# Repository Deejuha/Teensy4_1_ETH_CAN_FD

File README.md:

Teensy 4.1 shield with Ethernet, CAN FD and 2x CAN.

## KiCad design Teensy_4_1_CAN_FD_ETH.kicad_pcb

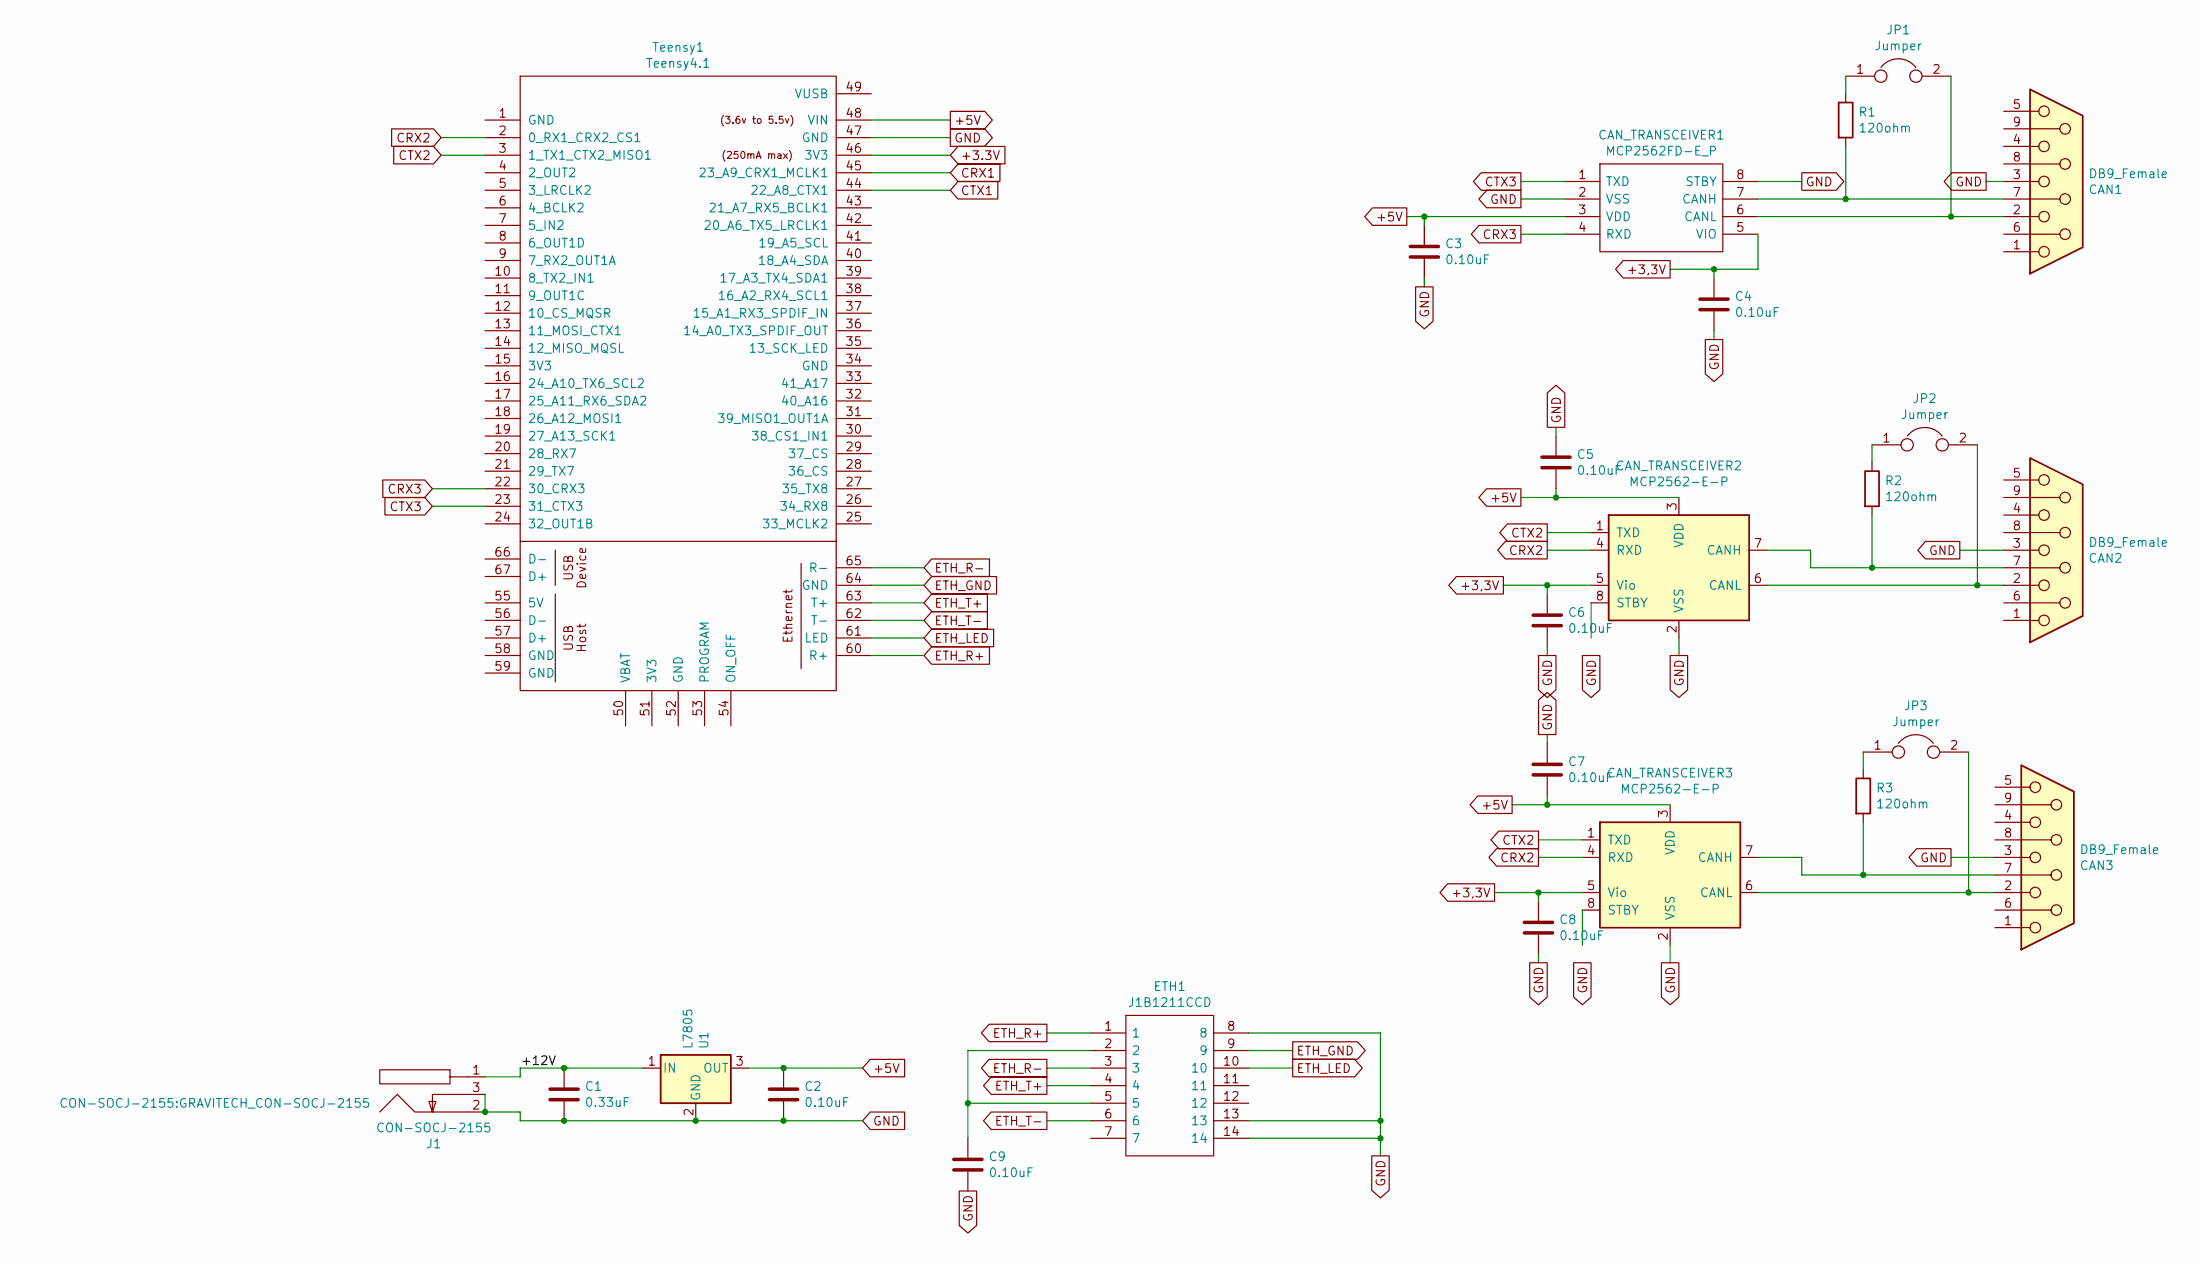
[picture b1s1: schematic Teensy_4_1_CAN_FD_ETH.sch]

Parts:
C1: 0.33uF; C_0603_1608Metric
C2, C3, C4, C5, C6, C7, C8, C9: 0.10uF; C_0603_1608Metric
CAN1, CAN2, CAN3: DB9_Female; DSUB-9_Female_Vertical_P2.77x2.84mm
CAN_TRANSCEIVER1: MCP2562FD-E_P; DIP787W46P254L927H533Q8; Mouser Part Number 579-MCP2562FD-E/P
CAN_TRANSCEIVER2, CAN_TRANSCEIVER3: MCP2562-E-P; DIP-8_W7.62mm
ETH1: J1B1211CCD; Mouser Part Number 950-J1B1211CCD
J1: CON-SOCJ-2155; GRAVITECH_CON-SOCJ-2155; Mouser Part Number 992-CON-SOCJ-2155
JP1, JP2, JP3: Jumper; PinSocket_1x02_P2.54mm_Vertical
R1, R2, R3: 120ohm; R_0603_1608Metric
Teensy1: Teensy4.1; Teensy41
U1: L7805; TO-220-3_Vertical

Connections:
+3,3V: C4.1, C6.1, C8.1, CAN_TRANSCEIVER1.5 (VIO), CAN_TRANSCEIVER2.5 (Vio), CAN_TRANSCEIVER3.5 (Vio)
+3.3V: Teensy1.46 (3V3)
+5V: C2.1, C3.1, C5.2, C7.2, CAN_TRANSCEIVER1.3 (VDD), CAN_TRANSCEIVER2.3 (VDD), CAN_TRANSCEIVER3.3 (VDD), Teensy1.48 (VIN), U1.3 (OUT)
/+12V: C1.1, J1.1, U1.1 (IN)
CRX1: Teensy1.45 (23_A9_CRX1_MCLK1)
CRX2: CAN_TRANSCEIVER2.4 (RXD), CAN_TRANSCEIVER3.4 (RXD), Teensy1.2 (0_RX1_CRX2_CS1)
CRX3: CAN_TRANSCEIVER1.4 (RXD), Teensy1.22 (30_CRX3)
CTX1: Teensy1.44 (22_A8_CTX1)
CTX2: CAN_TRANSCEIVER2.1 (TXD), CAN_TRANSCEIVER3.1 (TXD), Teensy1.3 (1_TX1_CTX2_MISO1)
CTX3: CAN_TRANSCEIVER1.1 (TXD), Teensy1.23 (31_CTX3)
ETH_GND: ETH1.9, Teensy1.64 (GND)
ETH_LED: ETH1.10, Teensy1.61 (LED)
ETH_R+: ETH1.1, Teensy1.60 (R+)
ETH_R-: ETH1.3, Teensy1.65 (R-)
ETH_T+: ETH1.4, Teensy1.63 (T+)
ETH_T-: ETH1.6, Teensy1.62 (T-)
GND: C1.2, C2.2, C3.2, C4.2, C5.1, C6.2, C7.1, C8.2, C9.2, CAN1.3, CAN2.3, CAN3.3, CAN_TRANSCEIVER1.2 (VSS), CAN_TRANSCEIVER1.8 (STBY), CAN_TRANSCEIVER2.2 (VSS), CAN_TRANSCEIVER3.2 (VSS), ETH1.8, ETH1.13, ETH1.14, J1.2, J1.3, Teensy1.47 (GND), U1.2 (GND)
unnamed: C9.1, ETH1.2, ETH1.5
unnamed: CAN1.2, CAN_TRANSCEIVER1.6 (CANL), JP1.2
unnamed: CAN1.7, CAN_TRANSCEIVER1.7 (CANH), R1.2
unnamed: CAN2.2, CAN_TRANSCEIVER2.6 (CANL), JP2.2
unnamed: CAN2.7, CAN_TRANSCEIVER2.7 (CANH), R2.2
unnamed: CAN3.2, CAN_TRANSCEIVER3.6 (CANL), JP3.2
unnamed: CAN3.7, CAN_TRANSCEIVER3.7 (CANH), R3.2
unnamed: JP1.1, R1.1
unnamed: JP2.1, R2.1
unnamed: JP3.1, R3.1

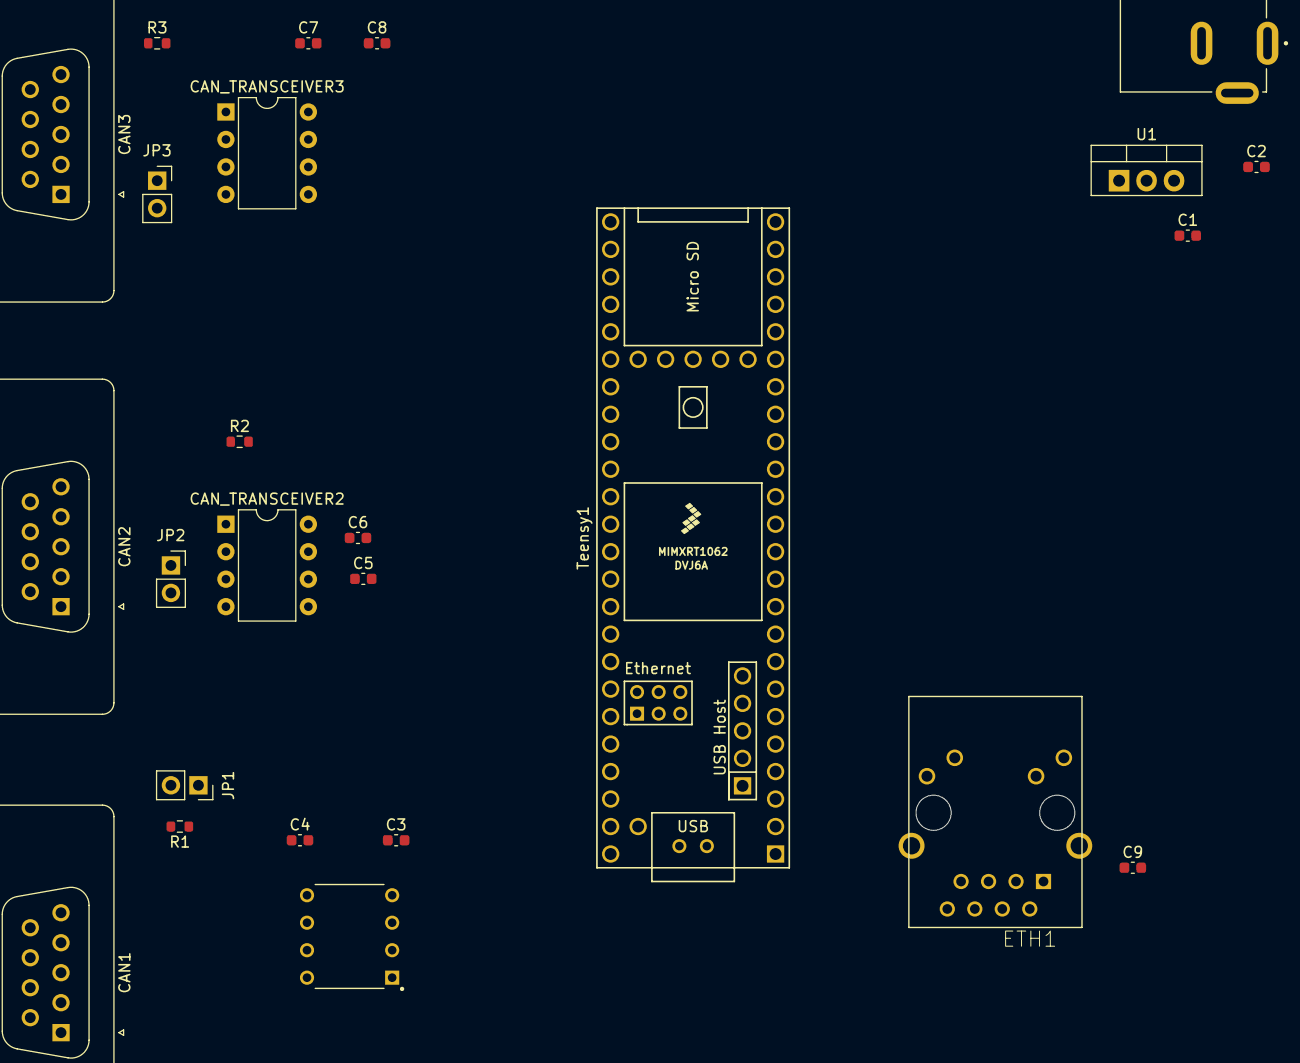
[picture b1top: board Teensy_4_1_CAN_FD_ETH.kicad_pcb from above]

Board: 2 copper layers, 25 parts (0 on the bottom side), 24 nets.

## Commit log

2021-03-27 Added boilerplate of KiCAD project, electronic schema
